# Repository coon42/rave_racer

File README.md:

# rave_racer
Things for an Arcade Machine from 1995 by Namco

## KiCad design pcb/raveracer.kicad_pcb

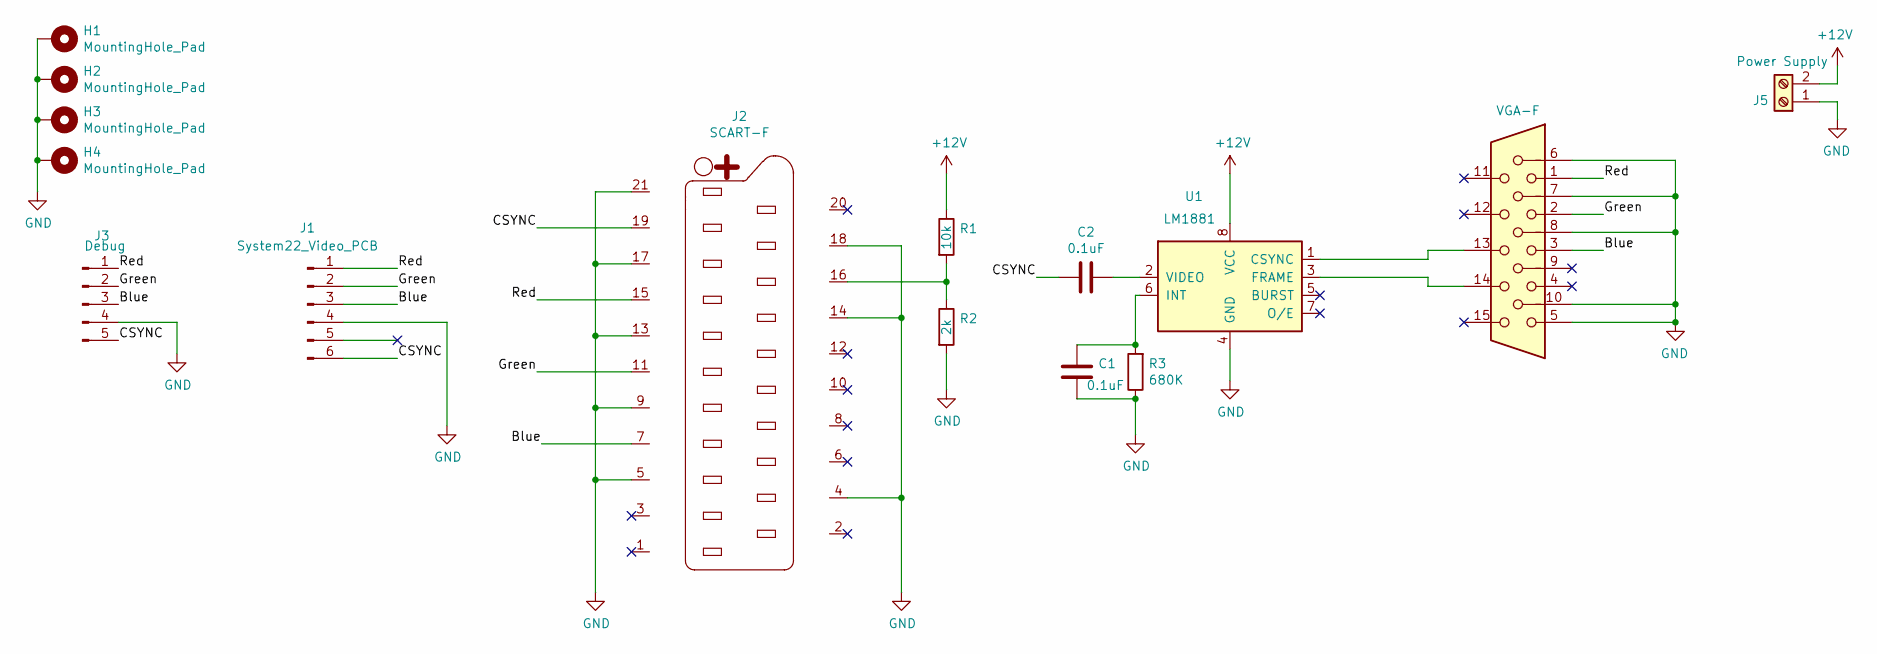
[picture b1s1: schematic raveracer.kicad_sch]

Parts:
C1, C2: 0.1uF; C_Disc_D3.0mm_W1.6mm_P2.50mm
H1, H2, H3, H4: MountingHole_Pad; MountingHole_3.5mm_Pad
J1: System22_Video_PCB; AMP-MODU-6
J2: SCART-F; SCART
J3: Debug; PinHeader_1x05_P2.54mm_Vertical
J4: VGA-F; DSUB-15-HD_Female_Horizontal_P2.29x1.98mm_EdgePinOffset8.35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
J5: Power Supply; TerminalBlock_Phoenix_MKDS-1,5-2-5.08_1x02_P5.08mm_Horizont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
R1: 10k; R_Axial_DIN0207_L6.3mm_D2.5mm_P7.62mm_Horizontal
R2: 2k; R_Axial_DIN0207_L6.3mm_D2.5mm_P7.62mm_Horizontal
R3: 680K; R_Axial_DIN0204_L3.6mm_D1.6mm_P5.08mm_Horizontal
U1: LM1881; DIP-8_W7.62mm

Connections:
+12V: J5.2, R1.1, U1.8 (VCC)
/Blue: J1.3, J2.7 (Blue), J3.3, J4.3
/CSYNC: C2.2, J1.6, J2.19, J3.5
/Green: J1.2, J2.11 (Green), J3.2, J4.2
/Red: J1.1, J2.15 (Red), J3.1, J4.1
GND: C1.2, H1.1, H2.1, H3.1, H4.1, J1.4, J2.4 (Audio_Ground), J2.5 (Blue_Video_Ground), J2.9 (Green_Video_Ground), J2.13 (Red_Video_Ground), J2.14 (Data_Ground), J2.17 (CSYNC_Ground), J2.18 (RGB_Switch_Ground), J2.21, J3.4, J4.5, J4.6, J4.7, J4.8, J4.10, J5.1, R2.2, R3.1, U1.4 (GND)
unnamed: C1.1, R3.2, U1.6 (INT)
unnamed: C2.1, U1.2 (VIDEO)
unnamed: J2.16 (RGB_Switch), R1.2, R2.1
unnamed: J4.13, U1.1 (CSYNC)
unnamed: J4.14, U1.3 (FRAME)

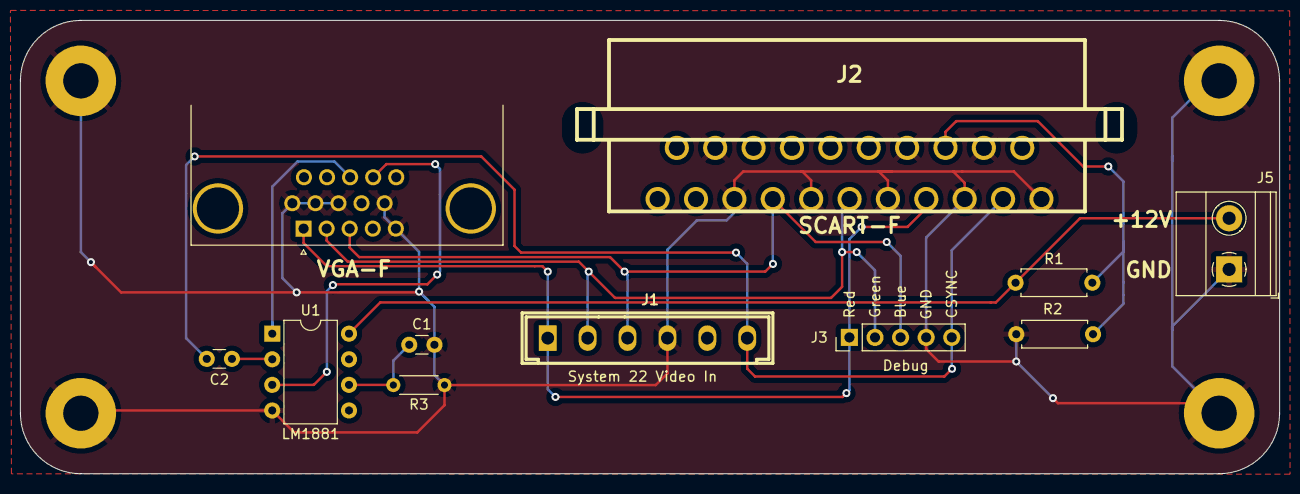
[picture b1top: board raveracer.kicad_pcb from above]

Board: 2 copper layers, 125.0 x 45.0 mm, 15 parts (0 on the bottom side), 11 nets.

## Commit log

2019-10-22 usb-gamecontroller: add README.md
2019-10-22 usb-gamecontroller: update README.md
2019-10-22 usb-gamecontroller: add Arduino code
2019-10-23 usb-gamecontroller: add arduino 1.8.10 / teensy library modifications
2019-10-24 usb_arcade: beautify / layout c++ interface to usb_arcade.cpp
2019-10-29 yield.cpp: reenable yield() for devices != USB_ARCADE
2019-10-29 usb-gamecontroller.ino: minimize code
2020-09-20 pcb: add routed pcb
2020-09-26 remove fp-info-cache + raveracer-cache.lib
2020-09-26 continue routing
2020-09-26 add rave_racer.lib with customized scart connector
2020-09-26 remove unused footprints
2020-10-16 finished routing of pcb
2020-10-16 add gerber files
2023-04-07 add ampmodu connector with proper pitch + did something on scart connector
2023-04-07 fix routing of modified ampmodu connector
2023-04-07 update gerber files
2023-04-07 add missing project files
